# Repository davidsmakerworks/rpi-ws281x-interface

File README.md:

# rpi-ws281x-interface
Interface to control WS281x LEDs with serial port on Raspberry Pi. This is a work in progress.

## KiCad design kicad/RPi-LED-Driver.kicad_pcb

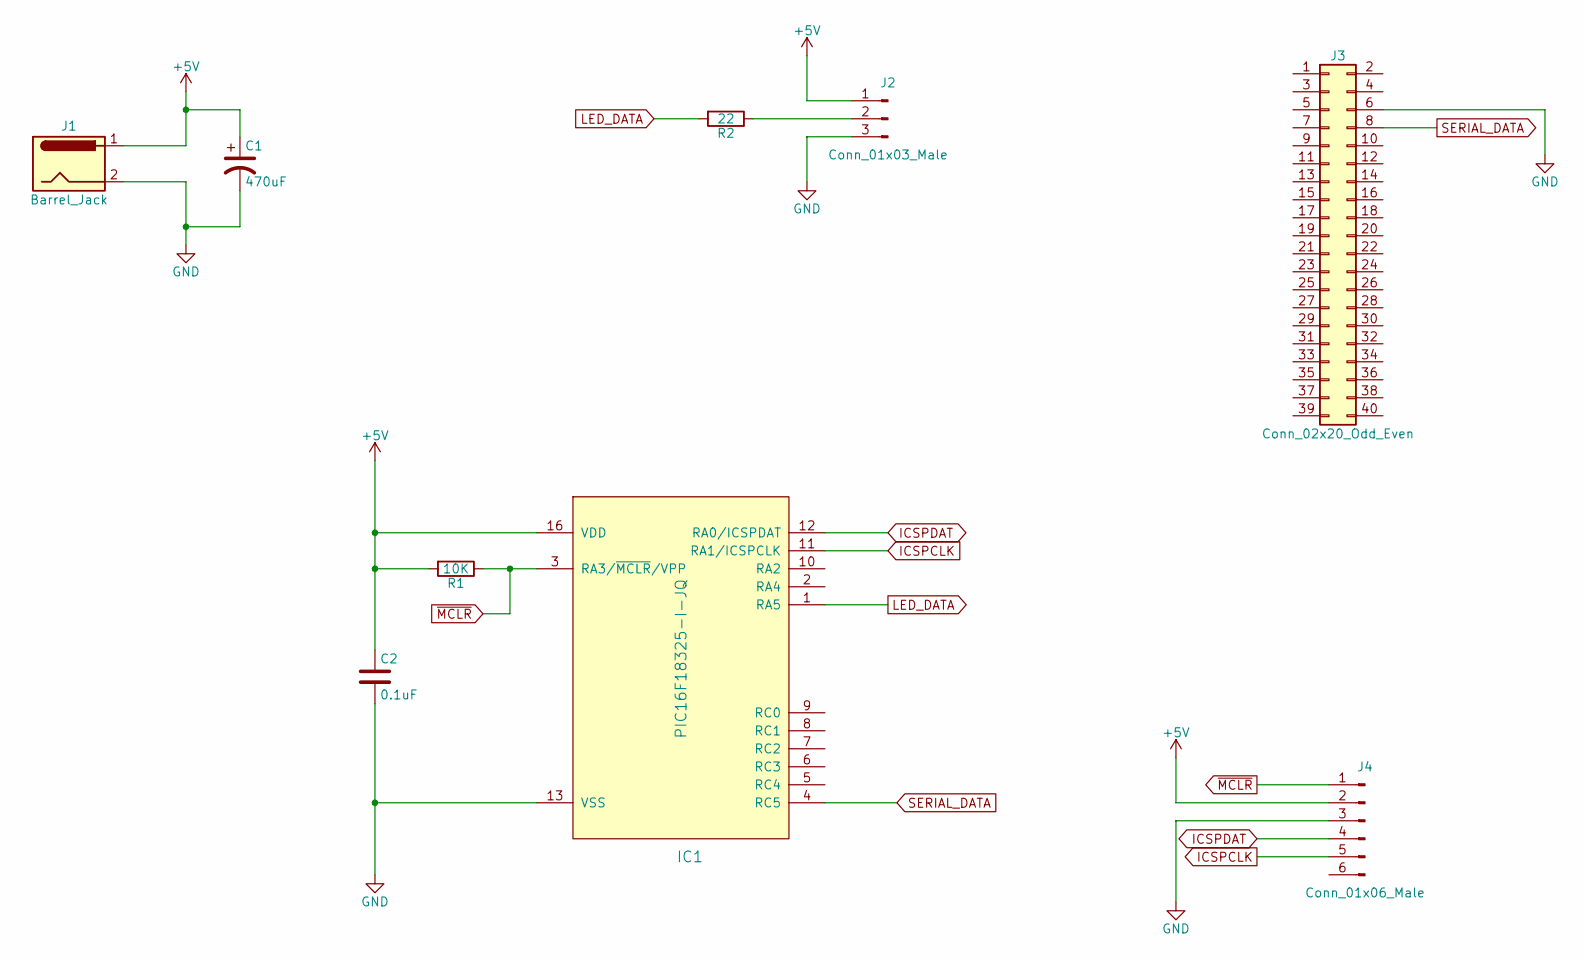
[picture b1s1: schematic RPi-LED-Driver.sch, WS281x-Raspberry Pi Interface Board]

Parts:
C1: 470uF; CP_Radial_D10.0mm_P5.00mm
C2: 0.1uF; C_0603_1608Metric
IC1: PIC16F18325-I-JQ; QFN-16-1EP_4x4mm_P0.65mm_EP2.1x2.1mm
J1: Barrel_Jack; BarrelJack_Horizontal
J2: Conn_01x03_Male; PinHeader_1x03_P2.54mm_Vertical
J3: Conn_02x20_Odd_Even; PinHeader_2x20_P2.54mm_Vertical
J4: Conn_01x06_Male; PinHeader_1x06_P2.54mm_Vertical
R1: 10K; R_0603_1608Metric
R2: 22; R_0805_2012Metric

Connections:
+5V: C1.1, C2.1, IC1.16 (VDD), J1.1, J2.1, J4.2, R1.2
GND: C1.2, C2.2, IC1.13 (VSS), J1.2, J2.3, J3.6, J4.3
ICSPCLK: IC1.11 (RA1/ICSPCLK), J4.5
ICSPDAT: IC1.12 (RA0/ICSPDAT), J4.4
LED_DATA: IC1.1 (RA5), R2.2
unnamed: J2.2, R2.1
SERIAL_DATA: IC1.4 (RC5), J3.8
~MCLR: IC1.3 (RA3/~MCLR~/VPP), J4.1, R1.1

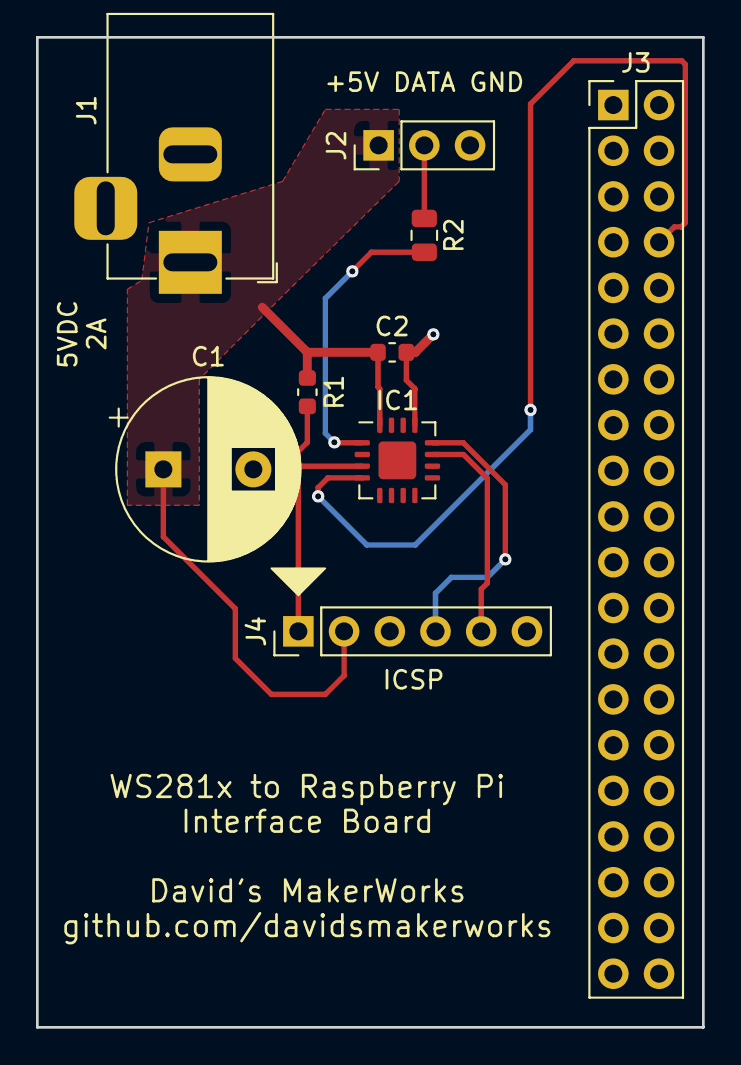
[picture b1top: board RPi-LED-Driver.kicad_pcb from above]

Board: 2 copper layers, 37.0 x 55.0 mm, 9 parts (0 on the bottom side), 8 nets.

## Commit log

2019-07-03 Set low-voltage programming entry
2019-07-14 Update project settings
2019-08-15 Update MPLXB X configurations
2019-09-28 Update brightness values
2019-11-01 Update DFP
2021-01-09 Remove unnecessary files
